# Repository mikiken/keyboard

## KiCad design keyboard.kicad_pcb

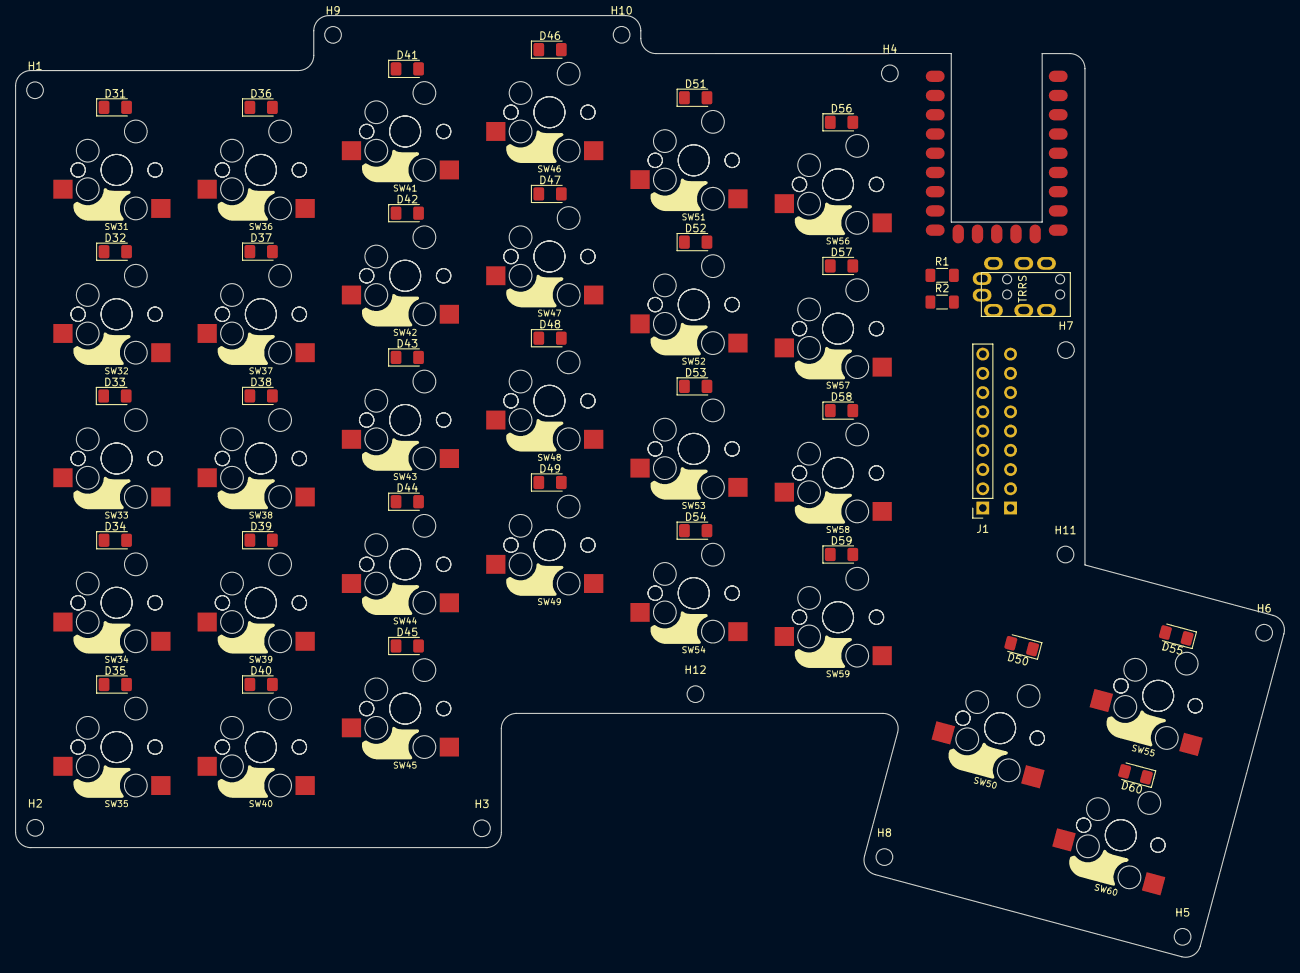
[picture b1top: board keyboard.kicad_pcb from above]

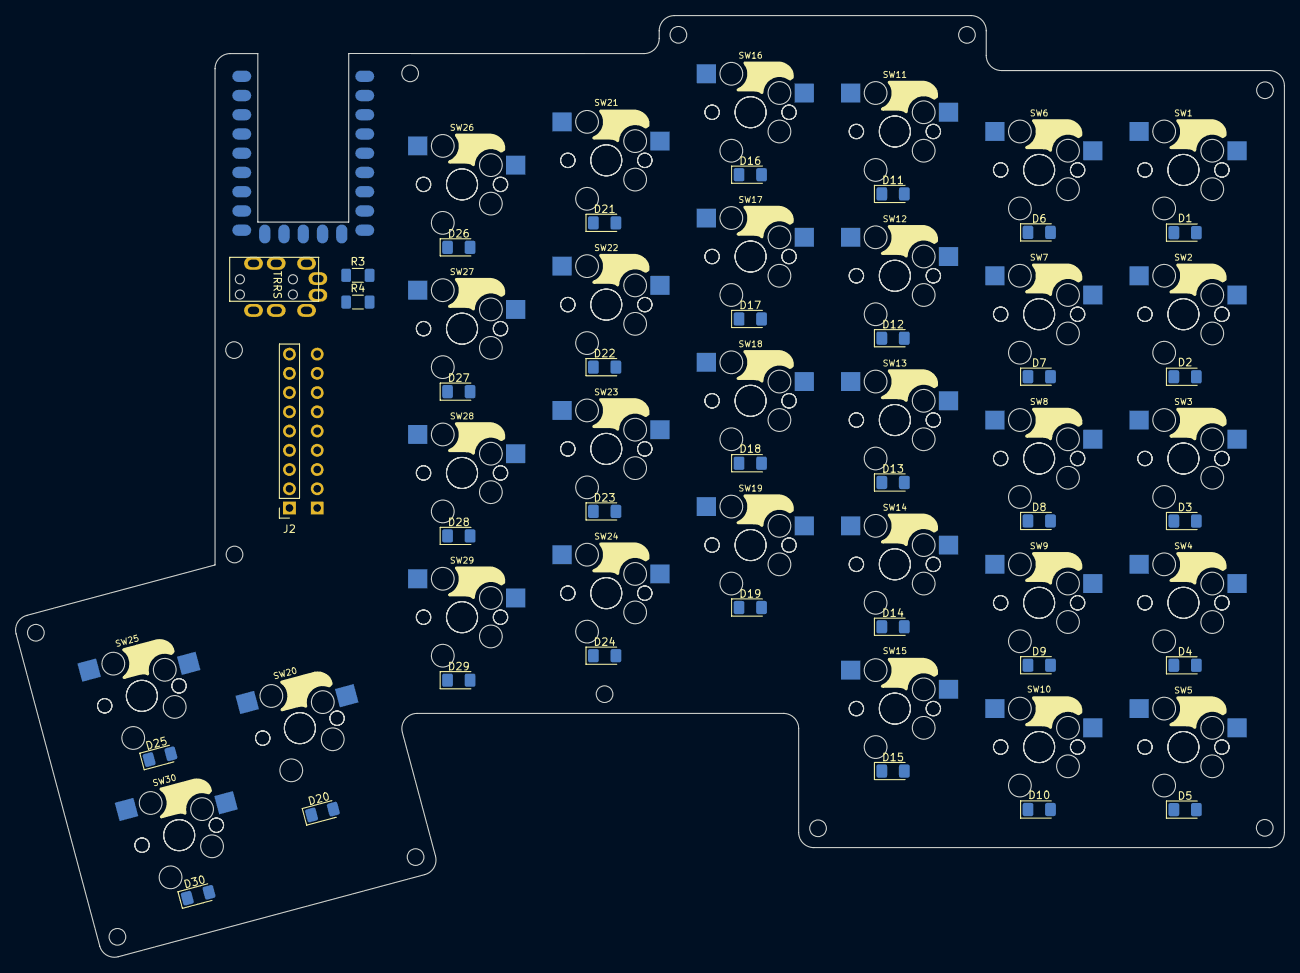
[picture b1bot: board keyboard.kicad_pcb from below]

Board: 2 copper layers, 167.5 x 124.3 mm, 142 parts (65 on the bottom side), 104 nets, no tracks yet.

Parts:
D1, D2, D3, D4, D5, D6, D7, D8, D9, D10, D11, D12, D13, D14, D15, D16, D17, D18, D19, D20, D21, D22, D23, D24, D25, D26, D27, D28, D29, D30, D31, D32, D33, D34, D35, D36, D37, D38, D39, D40, D41, D42, D43, D44, D45, D46, D47, D48, D49, D50, D51, D52, D53, D54, D55, D56, D57, D58, D59, D60: D; D_1206_3216Metric_Pad1.42x1.75mm_HandSolder
H1, H2, H3, H4, H5, H6, H7, H8, H9, H10, H11, H12: MountingHole; MountingHole_2.2mm_M2
J1, J2: Conn_01x09_Socket; PinSocket_1x09_P2.54mm_Vertical
JC1, JC2: AudioJack4; MJ-4PP-9
R1, R2, R3, R4: R; R_1206_3216Metric_Pad1.30x1.75mm_HandSolder
SW1, SW2, SW3, SW4, SW5, SW6, SW7, SW8, SW9, SW10, SW11, SW12, SW13, SW14, SW15, SW16, SW17, SW18, SW19, SW21, SW22, SW23, SW24, SW25, SW26, SW27, SW28, SW29, SW30, SW31, SW32, SW33, SW34, SW35, SW36, SW37, SW38, SW39, SW40, SW41, SW42, SW43, SW44, SW45, SW46, SW47, SW48, SW49, SW51, SW52, SW53, SW54, SW55, SW56, SW57, SW58, SW59, SW60: SW_Push; keyswitch_cherrymx_hotswap_1u
SW20, SW50: SW_Push; keyswitch_cherrymx_hotswap_2u_vertical
U1: rp2040-zero; rp2040-zero-smd_flush_front
U2: rp2040-zero; rp2040-zero-smd_flush_back

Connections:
unnamed: D1.2 (A), SW1.2
unnamed: D2.2 (A), SW2.2
unnamed: D3.2 (A), SW3.2
unnamed: D4.2 (A), SW4.2
unnamed: D5.2 (A), SW5.2
unnamed: D6.2 (A), SW6.2
unnamed: D7.2 (A), SW7.2
unnamed: D8.2 (A), SW8.2
unnamed: D9.2 (A), SW9.2
unnamed: D10.2 (A), SW10.2
unnamed: D11.2 (A), SW11.2
unnamed: D12.2 (A), SW12.2
unnamed: D13.2 (A), SW13.2
unnamed: D14.2 (A), SW14.2
unnamed: D15.2 (A), SW15.2
unnamed: D16.2 (A), SW16.2
unnamed: D17.2 (A), SW17.2
unnamed: D18.2 (A), SW18.2
unnamed: D19.2 (A), SW19.2
unnamed: D20.2 (A), SW20.2
unnamed: D21.2 (A), SW21.2
unnamed: D22.2 (A), SW22.2
unnamed: D23.2 (A), SW23.2
unnamed: D24.2 (A), SW24.2
unnamed: D25.2 (A), SW25.2
unnamed: D26.2 (A), SW26.2
unnamed: D27.2 (A), SW27.2
unnamed: D28.2 (A), SW28.2
unnamed: D29.2 (A), SW29.2
unnamed: D30.2 (A), SW30.2
unnamed: D31.2 (A), SW31.2
unnamed: D32.2 (A), SW32.2
unnamed: D33.2 (A), SW33.2
unnamed: D34.2 (A), SW34.2
unnamed: D35.2 (A), SW35.2
unnamed: D36.2 (A), SW36.2
unnamed: D37.2 (A), SW37.2
unnamed: D38.2 (A), SW38.2
unnamed: D39.2 (A), SW39.2
unnamed: D40.2 (A), SW40.2
unnamed: D41.2 (A), SW41.2
unnamed: D42.2 (A), SW42.2
unnamed: D43.2 (A), SW43.2
unnamed: D44.2 (A), SW44.2
unnamed: D45.2 (A), SW45.2
unnamed: D46.2 (A), SW46.2
unnamed: D47.2 (A), SW47.2
unnamed: D48.2 (A), SW48.2
unnamed: D49.2 (A), SW49.2
unnamed: D50.2 (A), SW50.2
unnamed: D51.2 (A), SW51.2
unnamed: D52.2 (A), SW52.2
unnamed: D53.2 (A), SW53.2
unnamed: D54.2 (A), SW54.2
unnamed: D55.2 (A), SW55.2
unnamed: D56.2 (A), SW56.2
unnamed: D57.2 (A), SW57.2
unnamed: D58.2 (A), SW58.2
unnamed: D59.2 (A), SW59.2
unnamed: D60.2 (A), SW60.2
unnamed: J1.1, U2.1 (0)
unnamed: J1.2, U2.2 (1)
unnamed: J1.3, U2.3 (2)
unnamed: J1.4, U2.4 (3)
unnamed: J1.5, U2.22 (GND)
unnamed: J1.6, R3.1, R4.1, U2.23 (5V)
unnamed: J1.7, U2.16 (15)
unnamed: J1.8, U2.19 (28)
unnamed: J1.9, U2.20 (29)
unnamed: J2.1, U1.1 (0)
unnamed: J2.2, U1.2 (1)
unnamed: J2.3, U1.3 (2)
unnamed: J2.4, U1.4 (3)
unnamed: J2.5, U1.22 (GND)
unnamed: J2.6, R1.1, R2.1, U1.23 (5V)
unnamed: J2.7, U1.16 (15)
unnamed: J2.8, U1.19 (28)
unnamed: J2.9, U1.20 (29)
unnamed: R1.2, U1.17 (26)
unnamed: R2.2, U1.18 (27)
unnamed: R3.2, U2.17 (26)
unnamed: R4.2, U2.18 (27)
l_col0: SW1.1, SW2.1, SW3.1, SW4.1, SW5.1, U1.5 (4)
l_col1: SW6.1, SW7.1, SW8.1, SW9.1, SW10.1, U1.6 (5)
l_col2: SW11.1, SW12.1, SW13.1, SW14.1, SW15.1, U1.7 (6)
l_col3: SW16.1, SW17.1, SW18.1, SW19.1, SW20.1, U1.8 (7)
l_col4: SW21.1, SW22.1, SW23.1, SW24.1, SW25.1, U1.9 (8)
l_col5: SW26.1, SW27.1, SW28.1, SW29.1, SW30.1, U1.10 (9)
l_row0: D1.1 (K), D6.1 (K), D11.1 (K), D16.1 (K), D21.1 (K), D26.1 (K), U1.11 (10)
l_row1: D2.1 (K), D7.1 (K), D12.1 (K), D17.1 (K), D22.1 (K), D27.1 (K), U1.12 (11)
l_row2: D3.1 (K), D8.1 (K), D13.1 (K), D18.1 (K), D23.1 (K), D28.1 (K), U1.13 (12)
l_row3: D4.1 (K), D9.1 (K), D14.1 (K), D19.1 (K), D24.1 (K), D29.1 (K), U1.14 (13)
l_row4: D5.1 (K), D10.1 (K), D15.1 (K), D20.1 (K), D25.1 (K), D30.1 (K), U1.15 (14)
r_col0: SW31.1, SW32.1, SW33.1, SW34.1, SW35.1, U2.5 (4)
r_col1: SW36.1, SW37.1, SW38.1, SW39.1, SW40.1, U2.6 (5)
r_col2: SW41.1, SW42.1, SW43.1, SW44.1, SW45.1, U2.7 (6)
r_col3: SW46.1, SW47.1, SW48.1, SW49.1, SW50.1, U2.8 (7)
r_col4: SW51.1, SW52.1, SW53.1, SW54.1, SW55.1, U2.9 (8)
r_col5: SW56.1, SW57.1, SW58.1, SW59.1, SW60.1, U2.10 (9)
r_row0: D31.1 (K), D36.1 (K), D41.1 (K), D46.1 (K), D51.1 (K), D56.1 (K), U2.11 (10)
r_row1: D32.1 (K), D37.1 (K), D42.1 (K), D47.1 (K), D52.1 (K), D57.1 (K), U2.12 (11)
r_row2: D33.1 (K), D38.1 (K), D43.1 (K), D48.1 (K), D53.1 (K), D58.1 (K), U2.13 (12)
r_row3: D34.1 (K), D39.1 (K), D44.1 (K), D49.1 (K), D54.1 (K), D59.1 (K), U2.14 (13)
r_row4: D35.1 (K), D40.1 (K), D45.1 (K), D50.1 (K), D55.1 (K), D60.1 (K), U2.15 (14)

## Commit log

2024-05-19 Create project
2024-05-19 Add key layout json file
2024-05-19 Add key and diode symbols
2024-05-19 Add `kleeb` as git submodule
2024-05-19 Add `kleeb` as 3rd-party library for Kicad
2024-05-20 Add Waveshare-RP2040 board and TRS jack
2024-05-23 Place all symbols on the schematic diagram
2024-05-23 Once got the schematic down to just one side.
2024-05-23 Add kbd as 3rd-party library for Kicad
2024-05-23 Fix import of footprints
2024-05-23 Apply footprints to each symbol
2024-05-24 回路図のアノテーションを変更
2024-05-24 キー配列を変更
2024-05-24 Add keyboard-layouter as git submodule
2024-05-24 部品のフットプリントを再設定
2024-05-24 フットプリント更新
2024-05-24 Init pcb
2024-05-25 なんとなく形になったので一旦commit
2024-05-25 キースイッチとダイオードを基板裏側に移動
2024-05-25 一旦保存2
2024-05-25 pcb大体並べたので一旦保存
2024-05-25 キースイッチをリバーシブルに配置できるよう穴の位置を調整
2024-05-30 実は耐えてた
2024-06-03 抵抗の配置を直したのでcommit
2024-06-19 とりまcommit
2024-11-10 基板外形完成
2024-11-10 ネジ穴を配置
